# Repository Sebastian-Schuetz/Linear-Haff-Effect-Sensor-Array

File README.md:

# Linear Haff Effect Sensor Array
The files for a simple linear Hall Effect Sensor Array, like the one shown below.
For more infos visit: [https://schuetzbuilds.de](https://schuetzbuilds.de/building-a-linear-hall-effect-sensor-array)

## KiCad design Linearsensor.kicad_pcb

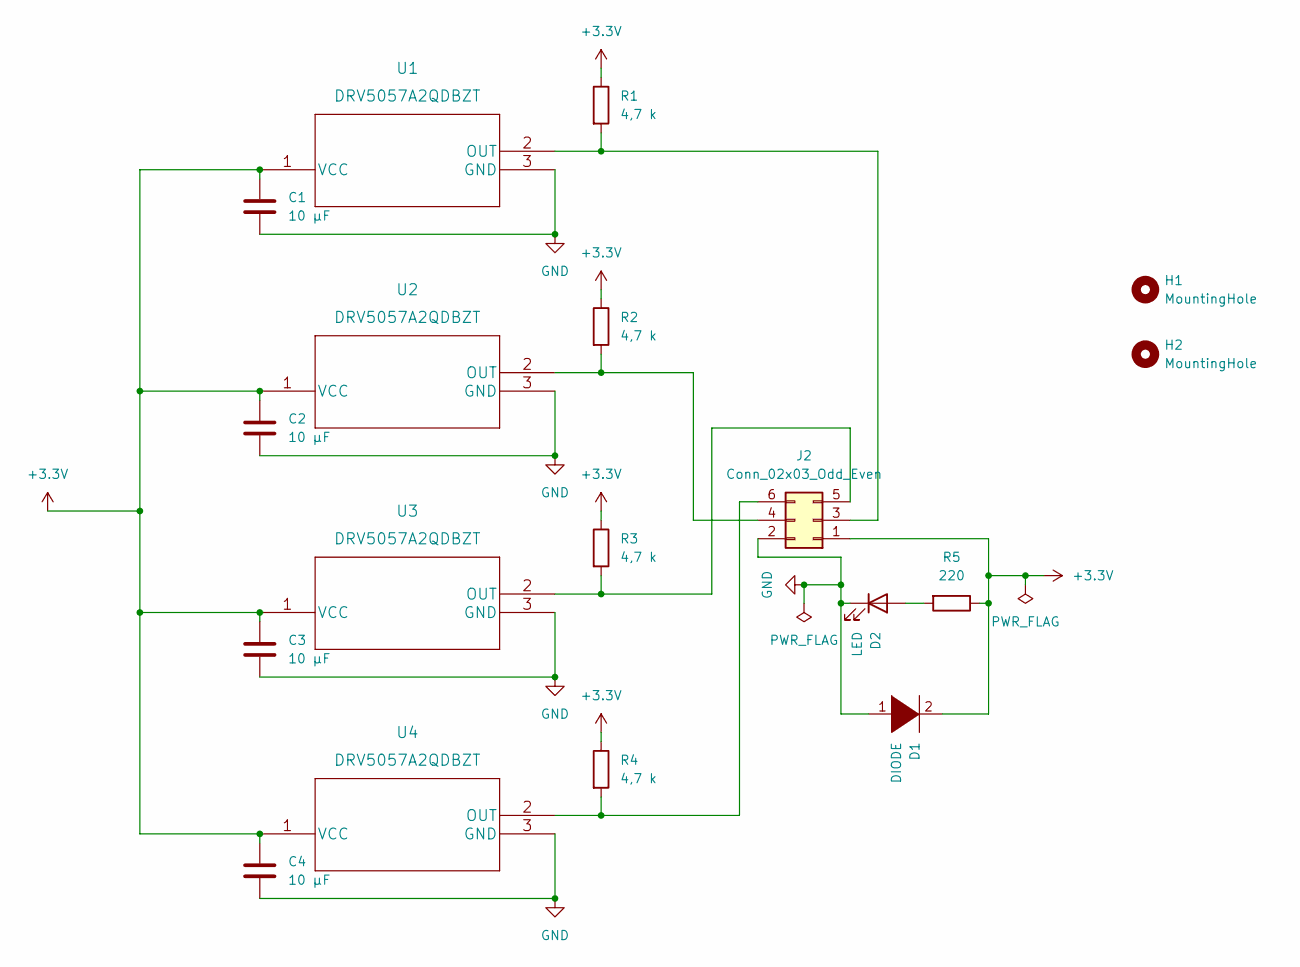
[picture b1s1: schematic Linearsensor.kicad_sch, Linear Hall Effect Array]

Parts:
C1, C2, C3, C4: 10 µF; C_0402_1005Metric
D1: DIODE; D_0603_1608Metric
D2: LED; LED_0603_1608Metric
H1, H2: MountingHole; MountingHole_2.1mm
J2: Conn_02x03_Odd_Even; PinHeader_2x03_P2.54mm_Horizontal
R1, R2, R3, R4: 4,7 k; R_0603_1608Metric
R5: 220; R_0603_1608Metric
U1, U2, U3, U4: DRV5057A2QDBZT; SOT-23

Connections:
+3.3V: C1.1, C2.1, C3.1, C4.1, D1.2 (A), J2.1, R1.1, R2.1, R3.1, R4.1, R5.1, U1.1 (VCC), U2.1 (VCC), U3.1 (VCC), U4.1 (VCC)
GND: C1.2, C2.2, C3.2, C4.2, D1.1 (K), D2.1 (K), J2.2, U1.3 (GND), U2.3 (GND), U3.3 (GND), U4.3 (GND)
unnamed: D2.2 (A), R5.2
unnamed: J2.3, R1.2, U1.2 (OUT)
unnamed: J2.4, R2.2, U2.2 (OUT)
unnamed: J2.5, R3.2, U3.2 (OUT)
unnamed: J2.6, R4.2, U4.2 (OUT)

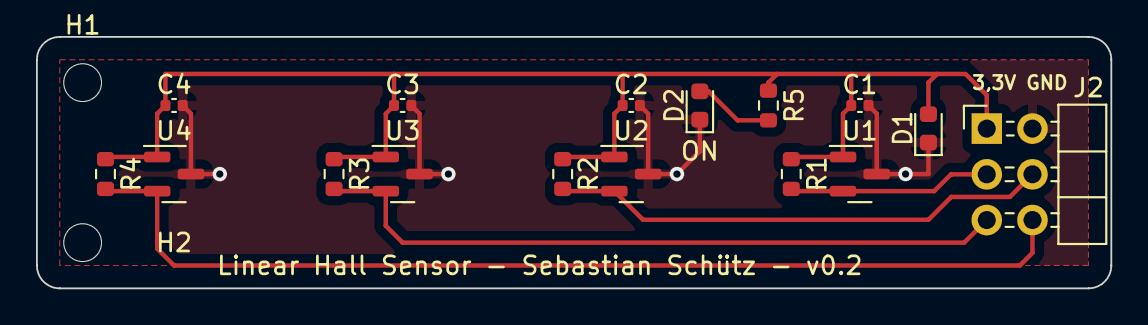
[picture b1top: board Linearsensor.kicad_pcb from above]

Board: 2 copper layers, 59.7 x 14.0 mm, 18 parts (0 on the bottom side), 7 nets.
